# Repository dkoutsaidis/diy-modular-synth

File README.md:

# diy-modular-synth
This repo hosts schematics and panel designs for varius DIY [eurorack](https://en.wikipedia.org/wiki/Eurorack) modules.

### Repo Structure
- The [main](https://github.com/dkoutsaidis/diy-modular-synth/tree/main) branch hosts already built and tested modules.
- The [develop](https://github.com/dkoutsaidis/diy-modular-synth/tree/develop) branch hosts modules that are currently being developed and/or tested.

### Analogue Modules
- [VCO/LFO - Digisound Project 80 - CEM3340](/VCO/Digisound%20CEM3340)
- [VCO/LFO - Nuts & Volts - CEM3340](/VCO/N%26V%20CEM3340)
- [VCO - All About Circuits](/VCO/AAC%20-%20Exponential%20VCO)
- [VCA - Skull & Circuits](/VCA/S%26C%20VCA)
- [AD/AR Envelope - Look Mum No Computer](/Envelope/LMNC%20-%20AD:AR)
- [SND/RTN - AISynthesis](/Utillity/AISynthesis%20SND:RTN)
- [Power Supply](/Power%20Supply)
- [Case](/Case)

### Digital Modules
- [CV Sequencer](https://github.com/dkoutsaidis/arduino-eurorack/tree/develop/cv_sequencer)
- [Gate Sequencer](https://github.com/dkoutsaidis/arduino-eurorack/tree/develop/gate_sequencer)

### Software
- Schematics and PCBs are created with the open-source [KiCad](https://kicad.org/) software (default libraries).
Specifications for the Power Supply, System Bus, CV & MIDI signals can be found [here](http://www.doepfer.de/a100_man/a100t_e.htm).
- Panel designs are created with the open-source [LibreCAD](https://librecad.org/) software.
Custom components can be found inside the [Panels Design Library](/Panels%20Design%20Library) folder. Specifications for eurorack panels can be found [here](http://www.doepfer.de/a100_man/a100m_e.htm).

### Stores
- electronic components bought from [here](https://grobotronics.com/)
- ICs bought from [here](https://electricdruid.net/)

### Useful Links
- [Books by Doepfer](http://www.doepfer.de/a100_man/a100b_e.htm)
- [More books for further reading](https://noisesculpture.com/)
- [DIY starter guide by Doepfer](http://www.doepfer.de/DIY/a100_diy.htm)
- [**MODULAR**Grid](https://www.modulargrid.net/e/users/view/192107)
- [MultisimLive](https://www.multisim.com/contributors/332247-dkoutsaidis/my-circuits/)
- [Module Tester](https://mutable-instruments.net/archive/module_tester/)

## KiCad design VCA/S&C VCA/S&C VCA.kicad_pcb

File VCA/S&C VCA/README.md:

# VCA - Skull & Circuits
A simple VCA module ([link](https://www.skullandcircuits.com/vca-1-2/)).

### Pros
- very simple design

### Cons
- no gain control, only CV passive attenuation

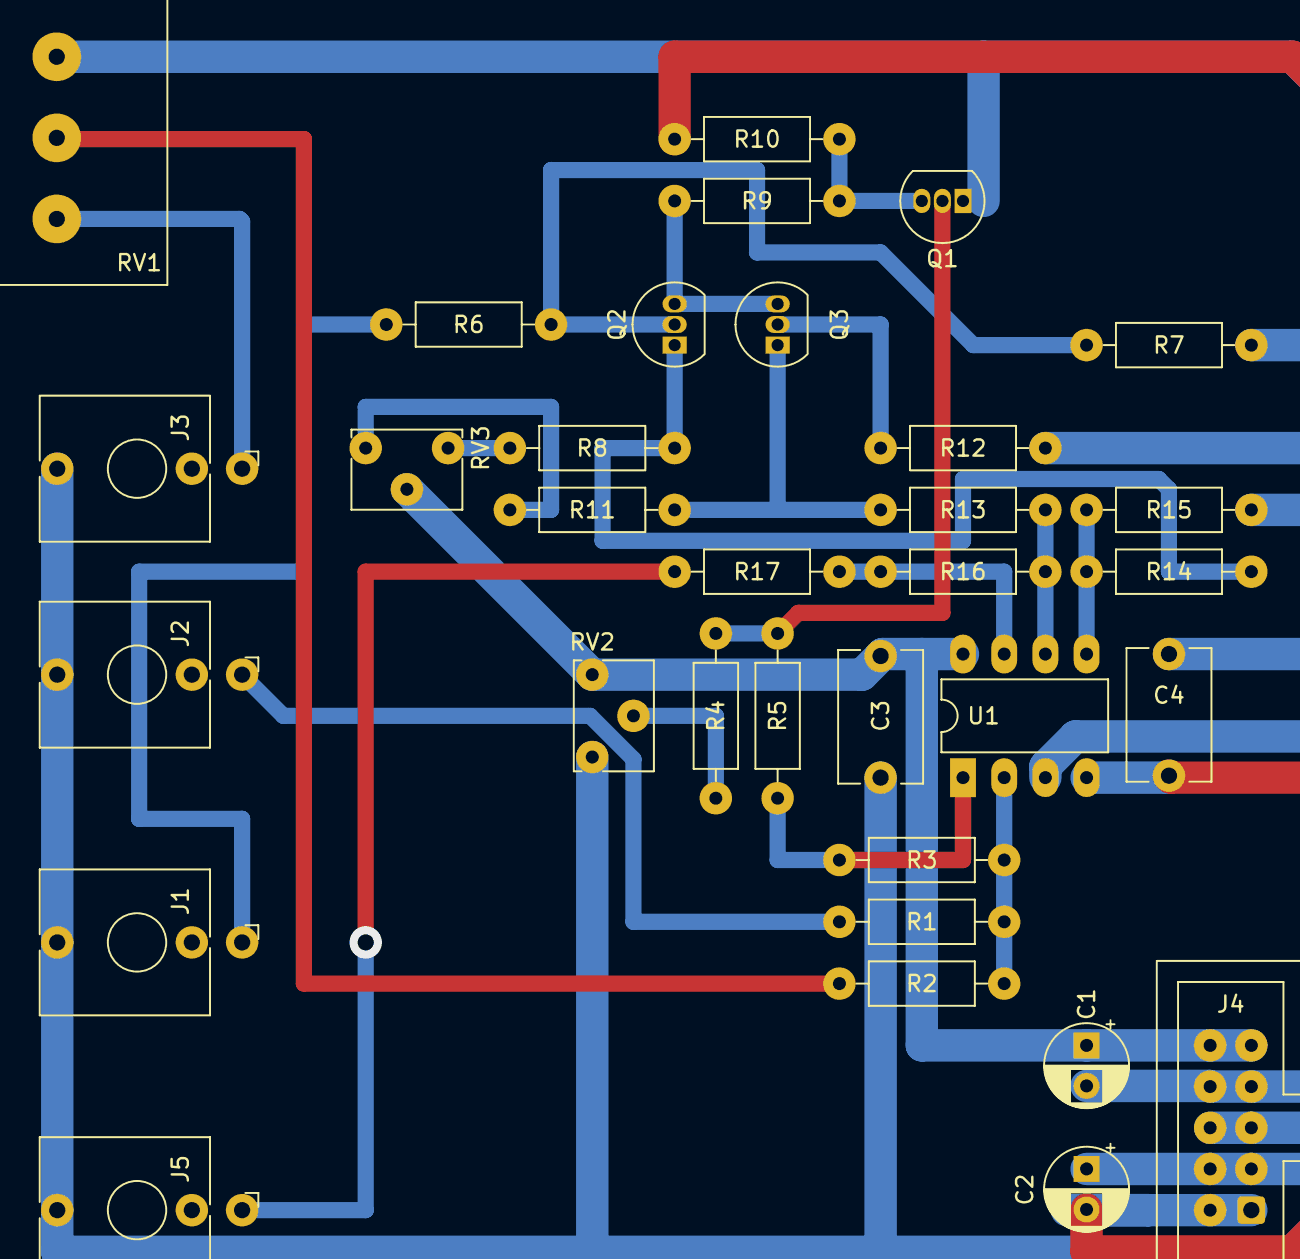
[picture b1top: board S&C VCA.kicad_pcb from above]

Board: 2 copper layers, 33 parts (0 on the bottom side), 22 nets.

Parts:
C1, C2: 10u; CP_Radial_D5.0mm_P2.50mm
C3, C4: 100n; C_Disc_D8.0mm_W5.0mm_P7.50mm
J1: Audio Input; Jack_3.5mm_QingPu_WQP-PJ398SM_Vertical_CircularHoles
J2: CV1; Jack_3.5mm_QingPu_WQP-PJ398SM_Vertical_CircularHoles
J3: CV2; Jack_3.5mm_QingPu_WQP-PJ398SM_Vertical_CircularHoles
J4: Power; IDC-Header_2x05_P2.54mm_Vertical
J5: Audio Output; Jack_3.5mm_QingPu_WQP-PJ398SM_Vertical_CircularHoles
Q1, Q2, Q3: BC550; TO-92_Inline
R1, R2, R3: 100k; R_Axial_DIN0207_L6.3mm_D2.5mm_P10.16mm_Horizontal
R4, R5, R10: 10k; R_Axial_DIN0207_L6.3mm_D2.5mm_P10.16mm_Horizontal
R6: 200k; R_Axial_DIN0207_L6.3mm_D2.5mm_P10.16mm_Horizontal
R7, R12, R17: 1k; R_Axial_DIN0207_L6.3mm_D2.5mm_P10.16mm_Horizontal
R8, R11, R13, R14: 15k; R_Axial_DIN0207_L6.3mm_D2.5mm_P10.16mm_Horizontal
R9: 33k; R_Axial_DIN0207_L6.3mm_D2.5mm_P10.16mm_Horizontal
R15, R16: 150k; R_Axial_DIN0207_L6.3mm_D2.5mm_P10.16mm_Horizontal
RV1: B100k; Potentiometer_Alps_RK163_Single_Horizontal
RV2, RV3: R_POT_TRIM; Potentiometer_Vishay_T73XX_Horizontal
U1: TL072; DIP-8_W7.62mm_LongPads

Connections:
+12V: C1.1, C3.2, J4.9, J4.10, RV2.1, RV3.2, U1.8
-12V: C2.2, C4.2, J4.1, J4.2, R10.2, U1.4
Earth: C1.2, C2.1, C3.1, C4.1, J1.T, J2.T, J3.T, J4.3, J4.4, J4.5, J4.6, J4.7, J4.8, J5.T, Q1.1, R7.2, R12.2, R15.1, RV1.1, RV2.3, U1.3
unnamed: J1.S, R6.1
unnamed: J2.S, R1.1
unnamed: J3.S, RV1.3
unnamed: J5.S, R17.1
unnamed: Q1.2, R4.2, R5.2
unnamed: Q1.3, R9.2, R10.1
unnamed: Q2.1, R8.2, R14.2
unnamed: Q2.2, R6.2, R7.1
unnamed: Q2.3, Q3.3, R9.1
unnamed: Q3.1, R11.2, R13.1
unnamed: Q3.2, R12.1
unnamed: R1.2, R2.2, R3.1, U1.2
unnamed: R3.2, R5.1, U1.1
unnamed: R4.1, RV2.2
unnamed: R8.1, RV3.1
unnamed: R11.1, RV3.3
unnamed: R13.2, R16.2, U1.6
unnamed: R14.1, R15.2, U1.5
unnamed: R16.1, R17.2, U1.7

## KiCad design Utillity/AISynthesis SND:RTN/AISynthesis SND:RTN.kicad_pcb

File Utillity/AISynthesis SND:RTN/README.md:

# SND/RTN - AISynthesis
A simple send/return module for IO with external guitar pedals ([link](https://aisynthesis.com/how-to-build-ai006-eurorack-send-return-module/)).

### Pros
- very simple design
- works excellent

### Cons
_

Next, there are some voltage-conversion-related useful info:

### Line Level
detailed info [here](https://en.wikipedia.org/wiki/Line_level)
| Use |	Nominal level	| Nominal level, VRMS |	Peak amplitude, VPK	| Peak-to-peak amplitude, VPP |
| --- | --- | --- | --- | --- |
| Professional | +4 dBu	| 1.228	| 1.736	| 3.472 |
| Consumer | −10 dBV | 0.316 |	0.447	| 0.894 |

### Microphone Level
We could roughly say that the microphone level is in the region of  -60dBV (0.001 volt) to -40dBV (0.010 volt).  

### Instrument Level
Electric guitars/basses supposedly put out around 0.15 to 0.5 volts p-p AC (some hotter humbucker guitars can put out over 1V p-p) and pedals can boost this quite a bit. The max theoretical output of any pedal is the available supply voltage (usually 9V p-p).  In reality, you hardly ever see this much because most devices don't operate rail-to-rail (some opamps do though). Generally, there is no safe limit on the output of a pedal.

### dBV / dB(VRMS)
Voltage relative to 1 volt, regardless of the impedance. This is used to measure microphone sensitivity, 
and also to specify the consumer line-level of −10 dBV, in order to reduce manufacturing costs relative to 
equipment using a +4 dBu line-level signal.

### dBu / dBv
RMS voltage relative to V=0.7746 (i.e. the voltage that would dissipate 1 mW into a 600Ω load). 
An RMS voltage of 1 V therefore corresponds to 2.218dBu.

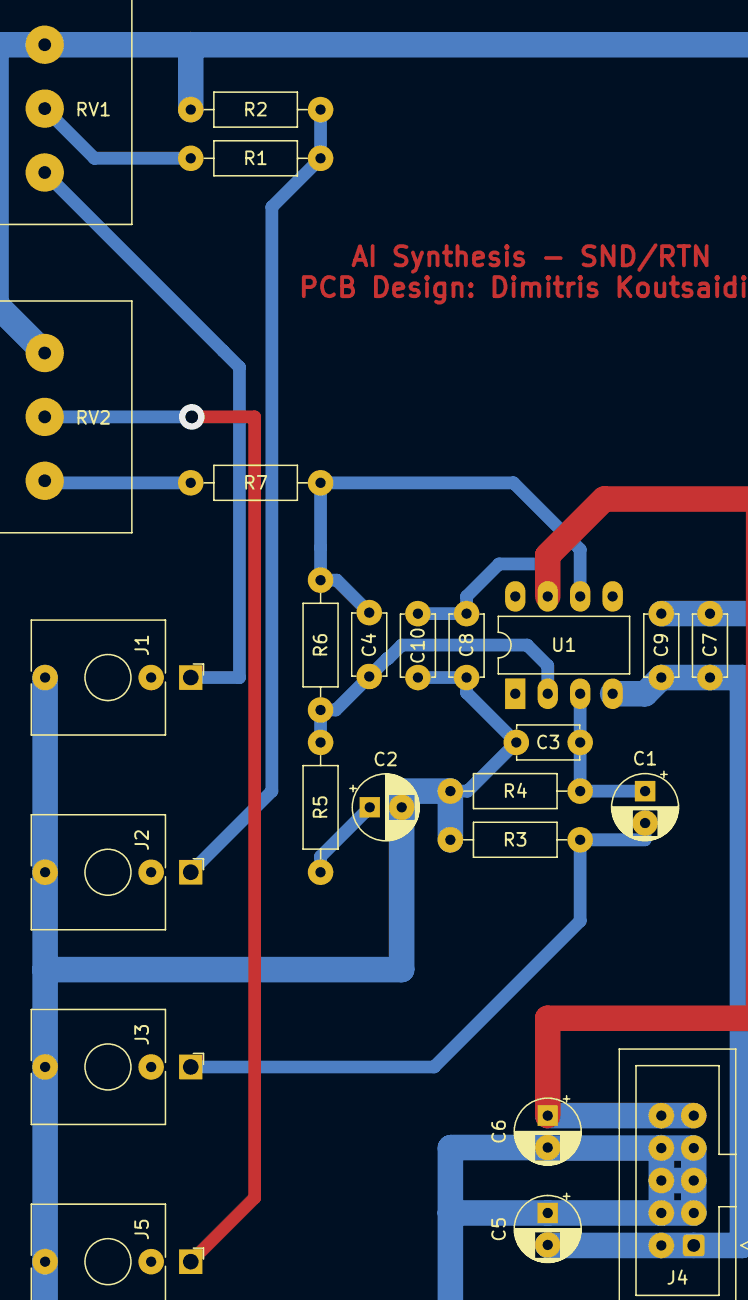
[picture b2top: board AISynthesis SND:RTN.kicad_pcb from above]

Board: 2 copper layers, 25 parts (0 on the bottom side), 14 nets.

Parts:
C1, C2, C5, C6: 10u; CP_Radial_D5.0mm_P2.50mm
C3: 10p; C_Disc_D4.7mm_W2.5mm_P5.00mm
C4: 47p; C_Disc_D4.7mm_W2.5mm_P5.00mm
C7, C8, C9, C10: 0.1u; C_Disc_D4.7mm_W2.5mm_P5.00mm
J1: Audio Input; Jack_3.5mm_QingPu_WQP-PJ398SM_Vertical_CircularHoles
J2: FX SND; Jack_3.5mm_QingPu_WQP-PJ398SM_Vertical_CircularHoles
J3: FX RTN; Jack_3.5mm_QingPu_WQP-PJ398SM_Vertical_CircularHoles
J4: Power; IDC-Header_2x05_P2.54mm_Vertical
J5: Audio Output; Jack_3.5mm_QingPu_WQP-PJ398SM_Vertical_CircularHoles
R1: 22k; R_Axial_DIN0207_L6.3mm_D2.5mm_P10.16mm_Horizontal
R2, R7: 1k; R_Axial_DIN0207_L6.3mm_D2.5mm_P10.16mm_Horizontal
R3: 1M; R_Axial_DIN0207_L6.3mm_D2.5mm_P10.16mm_Horizontal
R4: 150k; R_Axial_DIN0207_L6.3mm_D2.5mm_P10.16mm_Horizontal
R5: 470R; R_Axial_DIN0207_L6.3mm_D2.5mm_P10.16mm_Horizontal
R6: 10k; R_Axial_DIN0207_L6.3mm_D2.5mm_P10.16mm_Horizontal
RV1, RV2: 100k; Potentiometer_Alps_RK163_Single_Horizontal
U1: TL071; DIP-8_W7.62mm_LongPads

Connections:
+12V: C6.1, C8.2, C10.2, J4.9, J4.10, U1.7
-12V: C5.2, C7.1, C9.1, J4.1, J4.2, U1.4
GND: C2.2, C3.2, C5.1, C6.2, C7.2, C8.1, C9.2, C10.1, J1.T, J2.T, J3.T, J4.4, J4.6, J4.8, J5.T, R2.2, R3.2, R4.2, RV1.1, RV2.1
unnamed: C1.1, C3.1, R4.1, U1.3
unnamed: C1.2, J3.S, R3.1
unnamed: C2.1, R5.2
unnamed: C4.1, R6.1, R7.2, U1.6
unnamed: C4.2, R5.1, R6.2, U1.2
unnamed: J1.S, RV1.3
unnamed: J2.S, R1.2, R2.1
unnamed: J4.3, J4.5, J4.7
unnamed: J5.S, RV2.2
unnamed: R1.1, RV1.2
unnamed: R7.1, RV2.3

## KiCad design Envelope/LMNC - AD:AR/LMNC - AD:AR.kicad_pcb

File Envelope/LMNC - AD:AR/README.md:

# AD/AR Envelope - Look Mum No Computer
A simple Attack-Decay/Attack-Release envelope module ([link](https://www.lookmumnocomputer.com/projects#/simple-envelope-generator)).

### Pros
- Very simple design
- Fast attack

### Cons
- The Attack-Decay mode works best with trigger signals. The attack is not actually variable in this mode.
- The Attack-Release mode works best with gate signals.
- Requires at least 10Vp-p gate/trigger signals (positive-only).

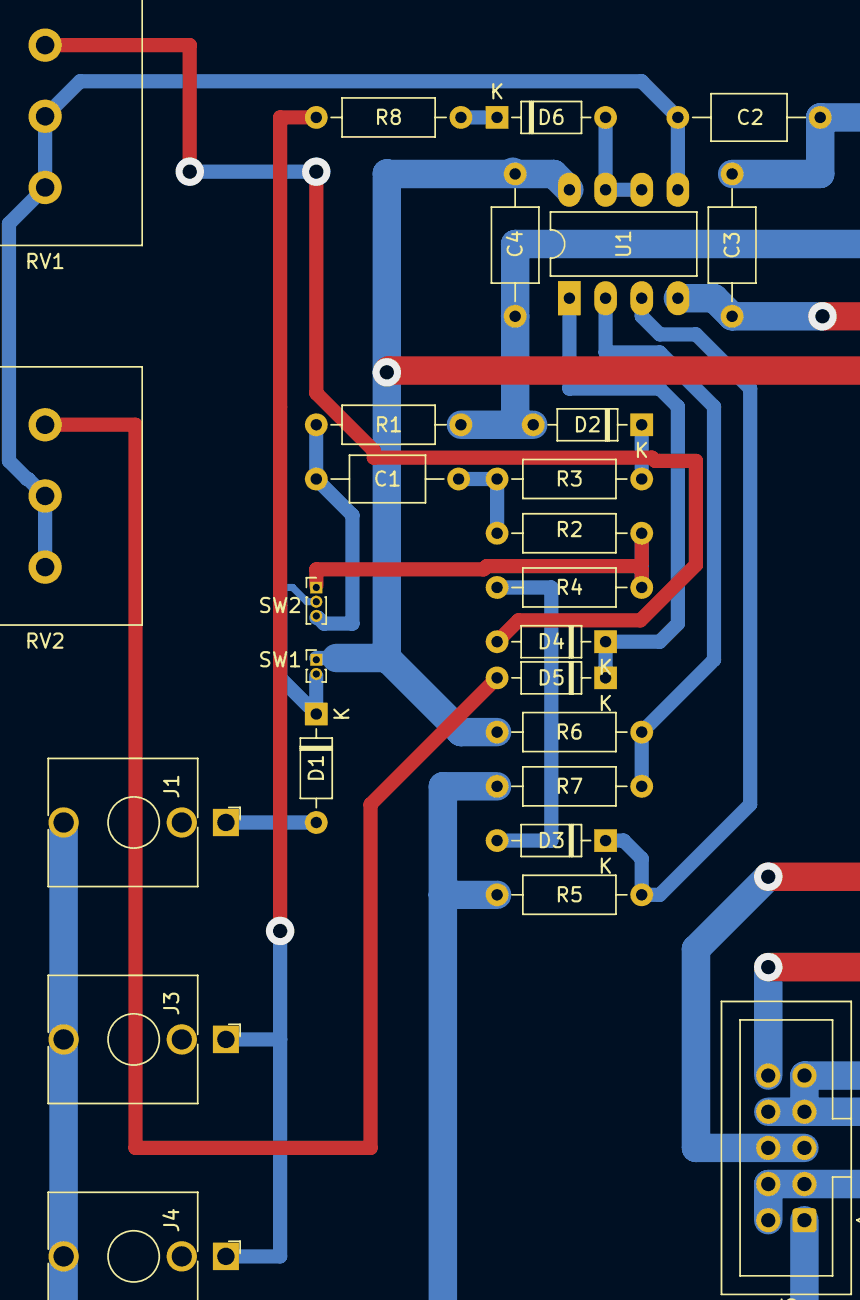
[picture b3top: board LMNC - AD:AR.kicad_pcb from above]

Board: 2 copper layers, 27 parts (0 on the bottom side), 19 nets.

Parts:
C1: 10n; C_Axial_L5.1mm_D3.1mm_P10.00mm_Horizontal
C2: C; C_Axial_L5.1mm_D3.1mm_P10.00mm_Horizontal
C3, C4: 100n; C_Axial_L5.1mm_D3.1mm_P10.00mm_Horizontal
D1, D2, D3, D4, D5, D6: 1N4148; D_DO-35_SOD27_P7.62mm_Horizontal
J1: Clock In; Jack_3.5mm_QingPu_WQP-PJ398SM_Vertical_CircularHoles
J2: Conn_02x05_Counter_Clockwise; IDC-Header_2x05_P2.54mm_Vertical
J3: Envelope Out 1; Jack_3.5mm_QingPu_WQP-PJ398SM_Vertical_CircularHoles
J4: Envelope Out 2; Jack_3.5mm_QingPu_WQP-PJ398SM_Vertical_CircularHoles
R1, R2, R5: 100k; R_Axial_DIN0207_L6.3mm_D2.5mm_P10.16mm_Horizontal
R3, R6: 47k; R_Axial_DIN0207_L6.3mm_D2.5mm_P10.16mm_Horizontal
R4, R7: 10k; R_Axial_DIN0207_L6.3mm_D2.5mm_P10.16mm_Horizontal
R8: 1k; R_Axial_DIN0207_L6.3mm_D2.5mm_P10.16mm_Horizontal
RV1, RV2: 1M; Potentiometer_Alps_RK163_Single_Horizontal
SW1: SW_Push; PinHeader_1x02_P1.00mm_Vertical
SW2: SW_DPDT_x2; PinHeader_1x03_P1.00mm_Vertical
U1: TL072; DIP-8_W7.62mm_LongPads

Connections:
+12V: C4.2, J2.5, J2.6, R6.1, SW1.1, U1.8
-12V: C3.1, J2.1, J2.10, U1.4
GND: C2.2, C3.2, C4.1, D2.2, J1.T, J2.2, J2.3, J2.4, J2.7, J2.8, J2.9, J3.T, J4.T, R1.2, R5.2, R7.2
unnamed: C1.1, R1.1, SW2.3
unnamed: C1.2, R2.1, R3.1
unnamed: C2.1, RV1.2, RV1.3, RV2.2, RV2.3, U1.5
unnamed: D1.1, SW1.2, SW2.2
unnamed: D1.2, J1.S
unnamed: D2.1, R3.2
unnamed: D3.1, R5.1, U1.3
unnamed: D3.2, R4.2
unnamed: D4.1, D5.1, U1.1
unnamed: D4.2, RV1.1
unnamed: D5.2, RV2.1
unnamed: D6.1, R8.2
unnamed: D6.2, U1.6, U1.7
unnamed: J3.S, J4.S, R8.1
unnamed: R2.2, R4.1, SW2.1
unnamed: R6.2, R7.1, U1.2

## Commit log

2021-03-23 add READMEs to create a dummy repo/folder structure
2021-03-23 add a dummy gitignore
2021-03-23 add the Look Mum No Computer - AD/AR module
2021-03-23 update gitignore
2021-03-23 add the AISynthesis - SND/RTN module
2021-03-23 add the Skull & Circuits - VCA module
2021-03-23 add the panel design of the Digisound Project 80 - VCO module
2021-03-23 add the panel design of the Nuts & Volts - VCO module
2021-03-23 add the design of the custom mono jack
2021-03-23 dummy README for the All About Circuits - Exponential VCO
2021-03-24 updated the gitignore file
2021-03-24 add dummy READMEs for my in-progress modules
2021-03-24 transfer the vactrol-based VCA to the correct parent folder
